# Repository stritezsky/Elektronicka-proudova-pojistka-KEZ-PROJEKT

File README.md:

# Elektronická proudová pojistka

Tento projekt představuje návrh a implementaci elektronické proudové pojistky, zadané v rámci cvičení KEZ na VUT FEKT v Brně. Cílem projektu bylo překreslit dodané schéma zapojení, navrhnout desku plošných spojů (DPS) s využitím softwaru KiCad a připravit projekt k odevzdání.

**Hlavní body projektu:**

* **Návrh DPS:** Vytvoření návrhu desky plošných spojů na základě dodaného schématu zapojení. Deska je navržena jako jednovrstvá nebo dvouvrstvá s ohledem na použití starších typů součástek (konstrukční třída 3 nebo 4).
* **Použité součástky:** Projekt zahrnuje klasické THT součástky, SMD součástky nebo jejich kombinaci. Důraz byl kladen na správné použití doporučených značek a pouzder z knihoven KiCadu.
* **Funkčnost:** Elektronická proudová pojistka je navržena k jištění elektrických obvodů proti nadměrnému proudu. Vypínací proud je nastavitelný pomocí konfigurace děliče napětí s rezistory R7 až R14 a propojky na kontaktních kolících KK1.
* **Napájení:** Pojistka je napájena stabilizovaným stejnosměrným napětím 12 V a obsahuje stabilizátor 78L05 pro získání referenčního napětí +5 V. Záporné napětí pro operační zesilovač je generováno astabilním multivibrátorem NE555 a zdvojovačem napětí.

**Technologie a nástroje:**

* **KiCad:** Návrh schématu a desky plošných spojů byl realizován v open-source EDA softwaru KiCad.
* **THT a SMD součástky:** Projekt zahrnuje návrh pro klasické průchozí (THT) i povrchově montované (SMD) součástky.

**Poznámky k vývoji:**

* Projekt byl vyvíjen v rámci individuálního cvičení BPC-KEZ pod vedením Ing. Pavla Hanáka, Ph.D.
* Při návrhu DPS bylo dbáno na správné rozmístění součástek a optimalizaci vedení spojů s ohledem na funkčnost a výrobitelnost desky.
* Byly zohledněny požadavky zadání, včetně možnosti použití jednovrstvé nebo dvouvrstvé desky a použití součástek s konstrukční třídou 3 nebo 4.

**Odevzdání projektu:**

Hotový KiCad projekt bude odevzdán ve stanoveném termínu. 

**Proč je tento projekt v mém CV?**

Tento projekt demonstruje mé schopnosti v oblasti:

* **Návrhu elektronických obvodů:** Pochopení schématu zapojení a jeho převedení do návrhu desky plošných spojů.
* **Práce s EDA nástroji:** Zkušenost s profesionálním softwarem pro návrh elektroniky KiCad.
* **Znalosti elektronických součástek:** Orientace v typech pouzder (THT, SMD) a jejich správném použití.
* **Řešení technických zadání:** Schopnost splnit zadané požadavky a odevzdat kompletní a funkční výsledek.
* **Samostatné práce na projektu:** Realizace individuálního projektu od zadání po finální návrh.

Schéma

PCB

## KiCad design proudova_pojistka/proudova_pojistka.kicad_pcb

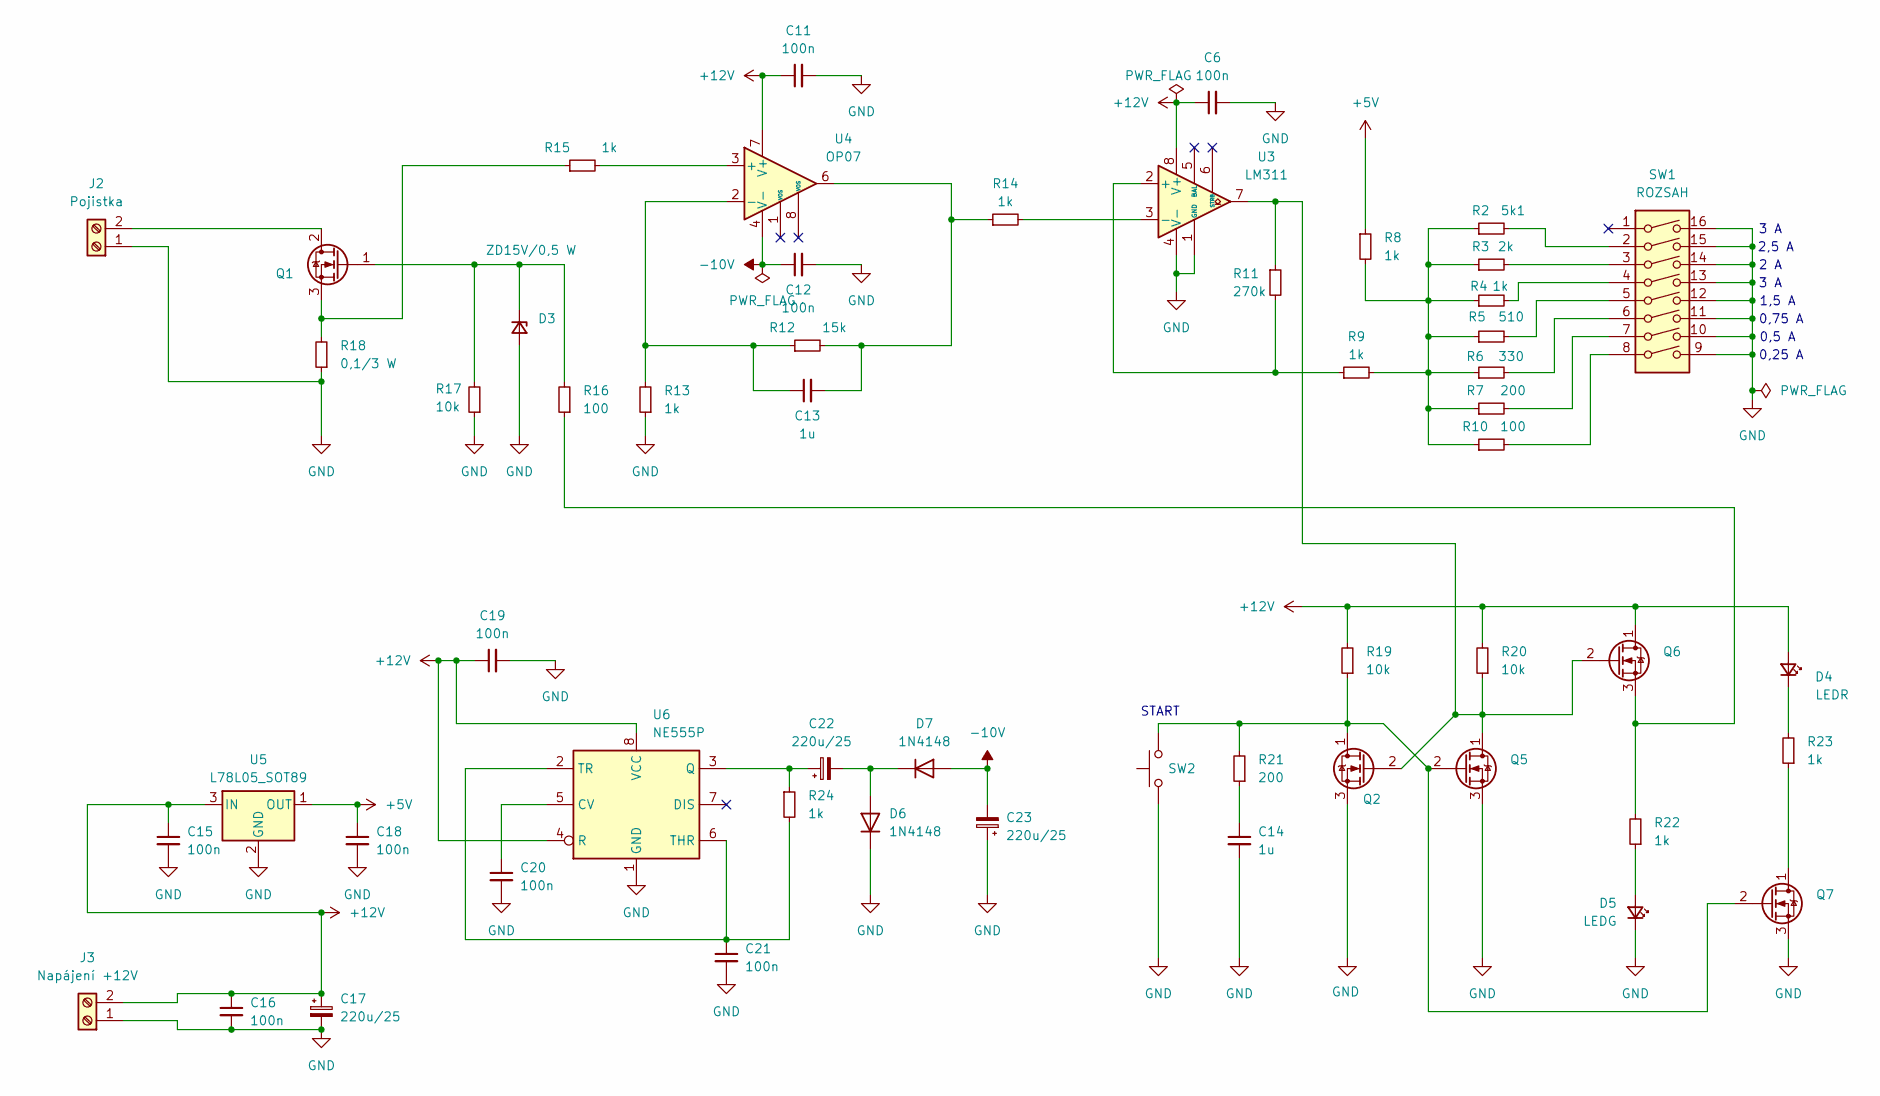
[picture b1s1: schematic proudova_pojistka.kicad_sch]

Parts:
C6, C11, C12, C15, C16, C18, C19, C20, C21: 100n; C_Disc_D5.0mm_W2.5mm_P5.00mm
C13, C14: 1u; C_Disc_D5.0mm_W2.5mm_P5.00mm
C17, C22, C23: 220u/25; CP_Radial_D8.0mm_P3.50mm
D3: ZD15V/0,5 W; D_DO-41_SOD81_P7.62mm_Horizontal
D4: LEDR; LED_D5.0mm
D5: LEDG; LED_D5.0mm
D6, D7: 1N4148; D_DO-35_SOD27_P7.62mm_Horizontal
J2: Pojistka; TerminalBlock_Phoenix_MKDS-1,5-2-5.08_1x02_P5.08mm_Horizont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
J3: Napájení +12V; TerminalBlock_Phoenix_MKDS-1,5-2-5.08_1x02_P5.08mm_Horizont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
Q1: Q_NMOS_GDS; TO-220-3_Vertical
Q2, Q5, Q6, Q7: BS170; TO-92_Inline
R2: 5k1; R_Axial_DIN0207_L6.3mm_D2.5mm_P7.62mm_Horizontal
R3: 2k; R_Axial_DIN0207_L6.3mm_D2.5mm_P7.62mm_Horizontal
R4, R8, R9, R13, R14, R15, R22, R23, R24: 1k; R_Axial_DIN0207_L6.3mm_D2.5mm_P7.62mm_Horizontal
R5: 510; R_Axial_DIN0207_L6.3mm_D2.5mm_P7.62mm_Horizontal
R6: 330; R_Axial_DIN0207_L6.3mm_D2.5mm_P7.62mm_Horizontal
R7, R21: 200; R_Axial_DIN0207_L6.3mm_D2.5mm_P7.62mm_Horizontal
R10, R16: 100; R_Axial_DIN0207_L6.3mm_D2.5mm_P7.62mm_Horizontal
R11: 270k; R_Axial_DIN0207_L6.3mm_D2.5mm_P7.62mm_Horizontal
R12: 15k; R_Axial_DIN0207_L6.3mm_D2.5mm_P7.62mm_Horizontal
R17, R19, R20: 10k; R_Axial_DIN0207_L6.3mm_D2.5mm_P7.62mm_Horizontal
R18: 0,1/3 W; R_Axial_DIN0918_L18.0mm_D9.0mm_P22.86mm_Horizontal
SW1: ROZSAH; SW_DIP_SPSTx08_Slide_9.78x22.5mm_W7.62mm_P2.54mm
SW2: SW_Push; SW_PUSH_6mm
U3: LM311; DIP-8_W7.62mm
U4: OP07; DIP-8_W7.62mm
U5: L78L05_SOT89; SOT-89-3
U6: NE555P; DIP-8_W7.62mm

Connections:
+5V: C18.1, R8.1, U5.1 (OUT)
+12V: C6.1, C11.1, C15.1, C16.1, C17.1, C19.1, D4.2 (A), J3.2, Q6.1 (D), R19.2, R20.2, U3.8 (V+), U4.7 (V+), U5.3 (IN), U6.4 (R), U6.8 (VCC)
-10V: C12.1, C23.2, D7.2 (A), U4.4 (V-)
GND: C6.2, C11.2, C12.2, C14.2, C15.2, C16.2, C17.2, C18.2, C19.2, C20.2, C21.2, C23.1, D3.2 (A), D5.1 (K), D6.1 (K), J2.1, J3.1, Q2.3 (S), Q5.3 (S), Q7.3 (S), R13.1, R17.1, R18.1, SW1.9, SW1.10, SW1.11, SW1.12, SW1.13, SW1.14, SW1.15, SW1.16, SW2.1, U3.1 (GND), U3.4 (V-), U5.2 (GND), U6.1 (GND)
unnamed: C13.2, R12.2, R14.1, U4.6
unnamed: C14.1, R21.1
unnamed: D3.1 (K), Q1.1 (G), R16.2, R17.2
unnamed: D4.1 (K), R23.2
unnamed: D5.2 (A), R22.1
unnamed: C22.2, D6.2 (A), D7.1 (K)
unnamed: J2.2, Q1.2 (D)
unnamed: Q1.3 (S), R15.1, R18.2
unnamed: Q2.1 (D), Q5.2 (G), Q7.2 (G), R19.1, R21.2, SW2.2
unnamed: Q2.2 (G), Q5.1 (D), Q6.2 (G), R11.1, R20.1, U3.7
unnamed: Q6.3 (S), R16.1, R22.2
unnamed: Q7.1 (D), R23.1
unnamed: R2.2, SW1.2
unnamed: R3.2, SW1.3
unnamed: R4.2, SW1.4
unnamed: R5.2, SW1.5
unnamed: R6.2, SW1.6
unnamed: R7.2, SW1.7
unnamed: R2.1, R3.1, R4.1, R5.1, R6.1, R7.1, R8.2, R9.2, R10.1
unnamed: R10.2, SW1.8
unnamed: R9.1, R11.2, U3.2 (+)
unnamed: R14.2, U3.3 (-)
unnamed: R15.2, U4.3 (+)
unnamed: C13.1, R12.1, R13.2, U4.2 (-)
unnamed: C20.1, U6.5 (CV)
unnamed: C22.1, R24.1, U6.3 (Q)
unnamed: C21.1, R24.2, U6.2 (TR), U6.6 (THR)

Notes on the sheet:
0,75 A
3 A
0,5 A
0,25 A
1,5 A
2 A
START
2,5 A

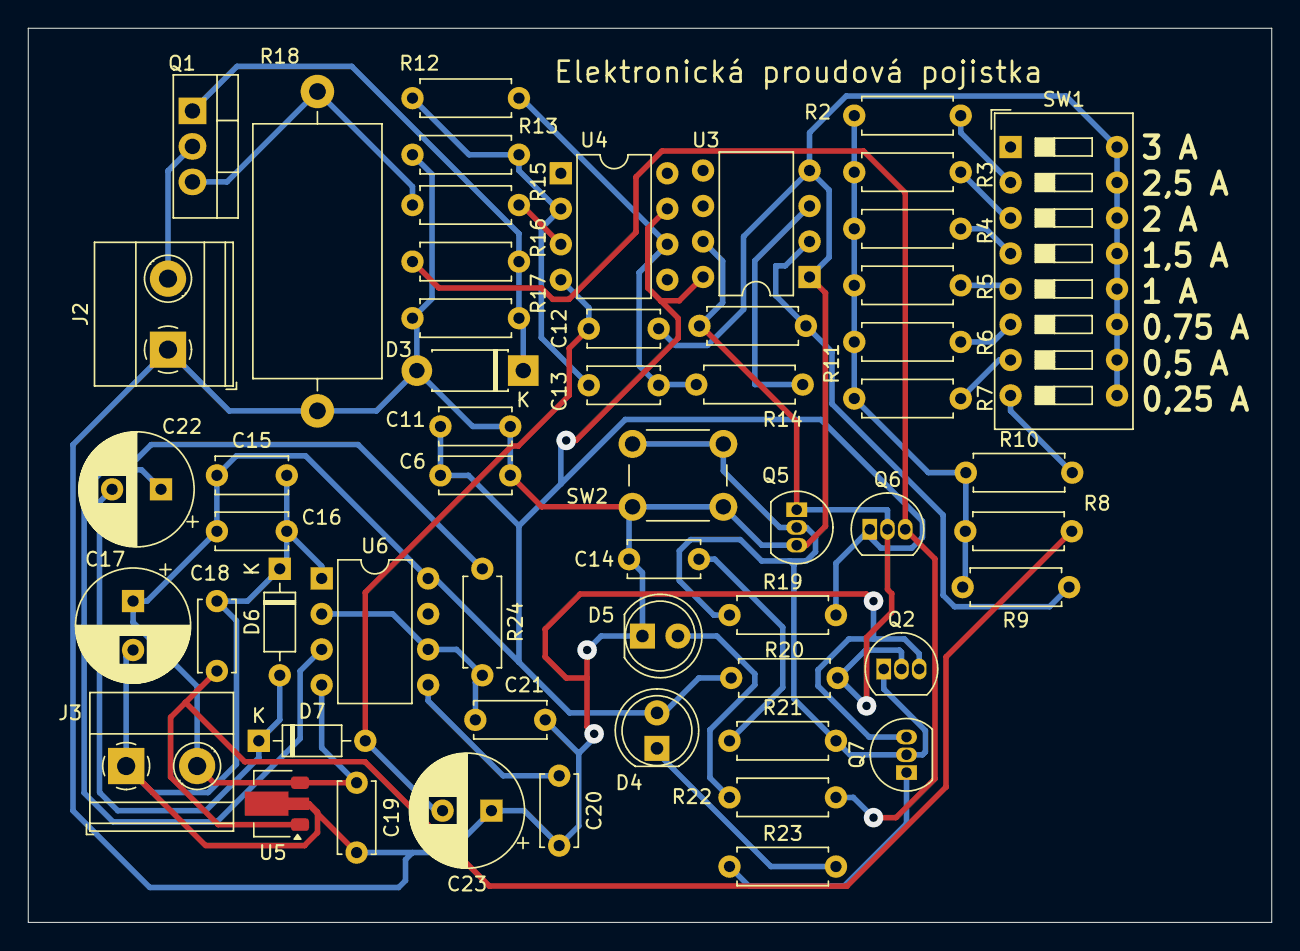
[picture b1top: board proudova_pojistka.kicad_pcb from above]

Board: 2 copper layers, 89.0 x 64.0 mm, 55 parts (0 on the bottom side), 31 nets.

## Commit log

2025-04-05 Rozdělení stran, příprava souborů...
2025-04-05 Vytvořen README.md
2025-04-08 Napájení
2025-04-11 Schéma + Footprinty
2025-04-16 Ready na konzultaci
2025-04-16 Squashed commit of the following:
    commit bc8b6beadf69644a5ea80d3999aa0f8eef698db1
    Author: stritezsky <stritezskyjirka@seznam.cz>
    Date: Wed Apr 16 21:45:37 2025 +0200
    Ready na konzultaci
    commit 592bed4c3ea77b2464c88108ae018bfdb5c68674
    Author: stritezsky <stritezskyjirka@seznam.cz>
2025-04-17 Odevzdaná verze - Přidaný ground plane
